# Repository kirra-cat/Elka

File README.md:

# Elka
Электронно-новогоднее, с Cortex и C... Вообщем, это инженерная ёлочка:)

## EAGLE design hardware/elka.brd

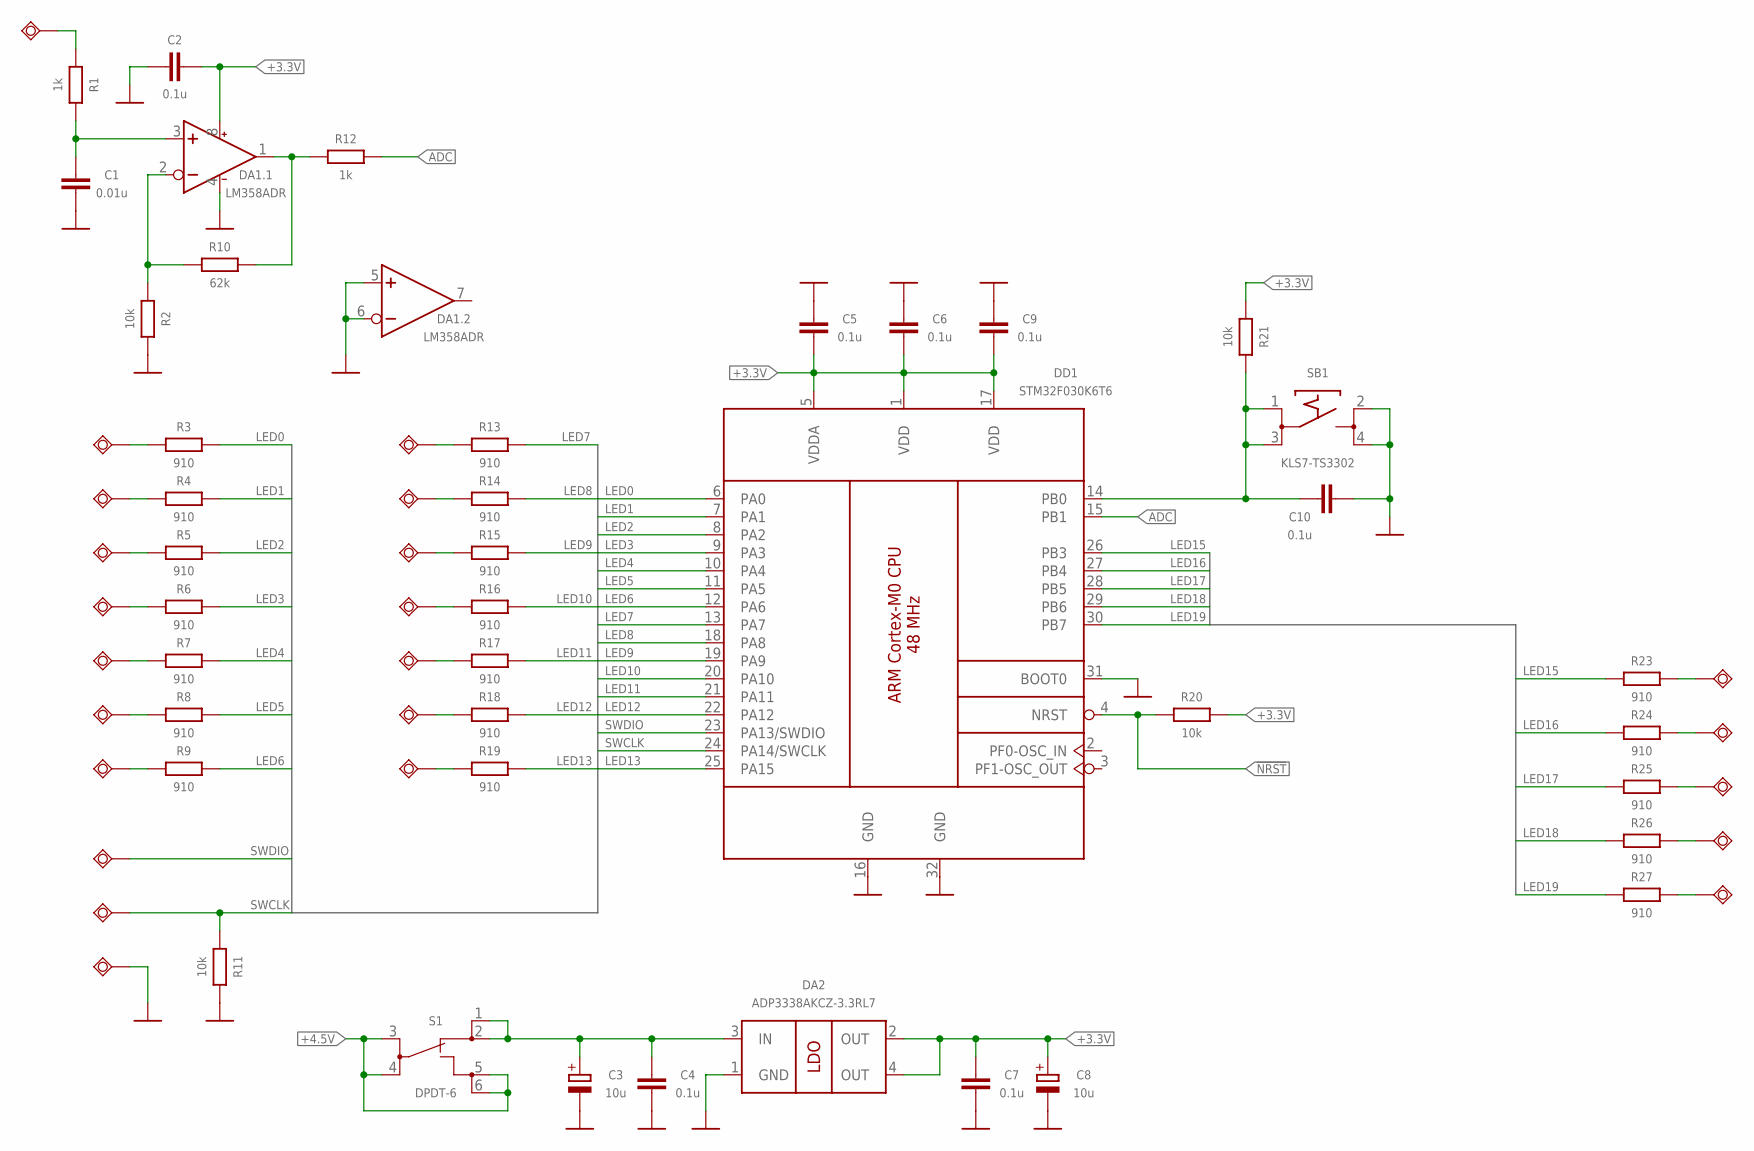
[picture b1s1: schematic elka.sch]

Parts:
C1: 0.01u; SMD0603
C2, C4, C5, C6, C7, C9, C10: 0.1u; SMD0603
C3, C8: 10u; SMC_B
DA1: LM358ADR; SOIC8
DA2: ADP3338AKCZ-3.3RL7; SOT223-W
DD1: STM32F030K6T6; LQFP32
R1, R12: 1k; SMD0603
R2, R11, R20, R21: 10k; SMD0603
R3, R4, R5, R6, R7, R8, R9, R13, R14, R15, R16, R17, R18, R19, R23, R24, R25, R26, R27: 910; SMD0603
R10: 62k; SMD0603
S1: DPDT-6; DPDT
SB1: KLS7-TS3302
TP1, TP2, TP3, TP4, TP5, TP6, TP7, TP8, TP9, TP10, TP11, TP12, TP13, TP14, TP15, TP16, TP17, TP19, TP20, TP21, TP22, TP23, TP24: TPSQTP20R; TP20R

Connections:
!NRST: DD1.4 (NRST), R20.1
+3.3V: C2.2, C5.2, C6.2, C7.1, C8.+, C9.2, DA1.8 (VCC+), DA2.2 (OUT), DA2.4 (OUT), DD1.1 (VDD), DD1.5 (VDDA), DD1.17 (VDD), R20.2, R21.2
+4.5V: S1.3, S1.4, S1.5, S1.6
ADC: DD1.15 (PB1), R12.1
GND: C1.2, C2.1, C3.-, C4.2, C5.1, C6.1, C7.2, C8.-, C9.1, C10.2, DA1.4 (VCC-), DA1.5 (IN+), DA1.6 (IN-), DA2.1 (GND), DD1.16 (GND), DD1.31 (BOOT0), DD1.32 (GND), R2.1, R11.2, SB1.2, SB1.4, TP1.TP
LED0: DD1.6 (PA0), R3.1
LED1: DD1.7 (PA1), R4.1
LED2: DD1.8 (PA2), R5.1
LED3: DD1.9 (PA3), R6.1
LED4: DD1.10 (PA4), R7.1
LED5: DD1.11 (PA5), R8.1
LED6: DD1.12 (PA6), R9.1
LED7: DD1.13 (PA7), R13.1
LED8: DD1.18 (PA8), R14.1
LED9: DD1.19 (PA9), R15.1
LED10: DD1.20 (PA10), R16.1
LED11: DD1.21 (PA11), R17.1
LED12: DD1.22 (PA12), R18.1
LED13: DD1.25 (PA15), R19.1
LED15: DD1.26 (PB3), R23.1
LED16: DD1.27 (PB4), R24.1
LED17: DD1.28 (PB5), R25.1
LED18: DD1.29 (PB6), R26.1
LED19: DD1.30 (PB7), R27.1
unnamed: R14.2, TP2.TP
unnamed: C1.1, DA1.3 (IN+), R1.1
unnamed: R15.2, TP3.TP
unnamed: R16.2, TP4.TP
unnamed: R17.2, TP5.TP
unnamed: R18.2, TP6.TP
unnamed: DA1.2 (IN-), R2.2, R10.2
unnamed: R19.2, TP9.TP
unnamed: DA1.1 (OUT), R10.1, R12.2
unnamed: R3.2, TP10.TP
unnamed: R4.2, TP11.TP
unnamed: R5.2, TP12.TP
unnamed: R6.2, TP13.TP
unnamed: R7.2, TP14.TP
unnamed: R8.2, TP15.TP
unnamed: R13.2, TP17.TP
unnamed: R9.2, TP16.TP
unnamed: C3.+, C4.1, DA2.3 (IN), S1.1, S1.2
unnamed: R23.2, TP19.TP
unnamed: R24.2, TP20.TP
unnamed: R25.2, TP21.TP
unnamed: R26.2, TP22.TP
unnamed: R27.2, TP23.TP
unnamed: C10.1, DD1.14 (PB0), R21.1, SB1.1, SB1.3
unnamed: R1.2, TP24.TP
SWCLK: DD1.24 (PA14/SWCLK), R11.1, TP8.TP
SWDIO: DD1.23 (PA13/SWDIO), TP7.TP

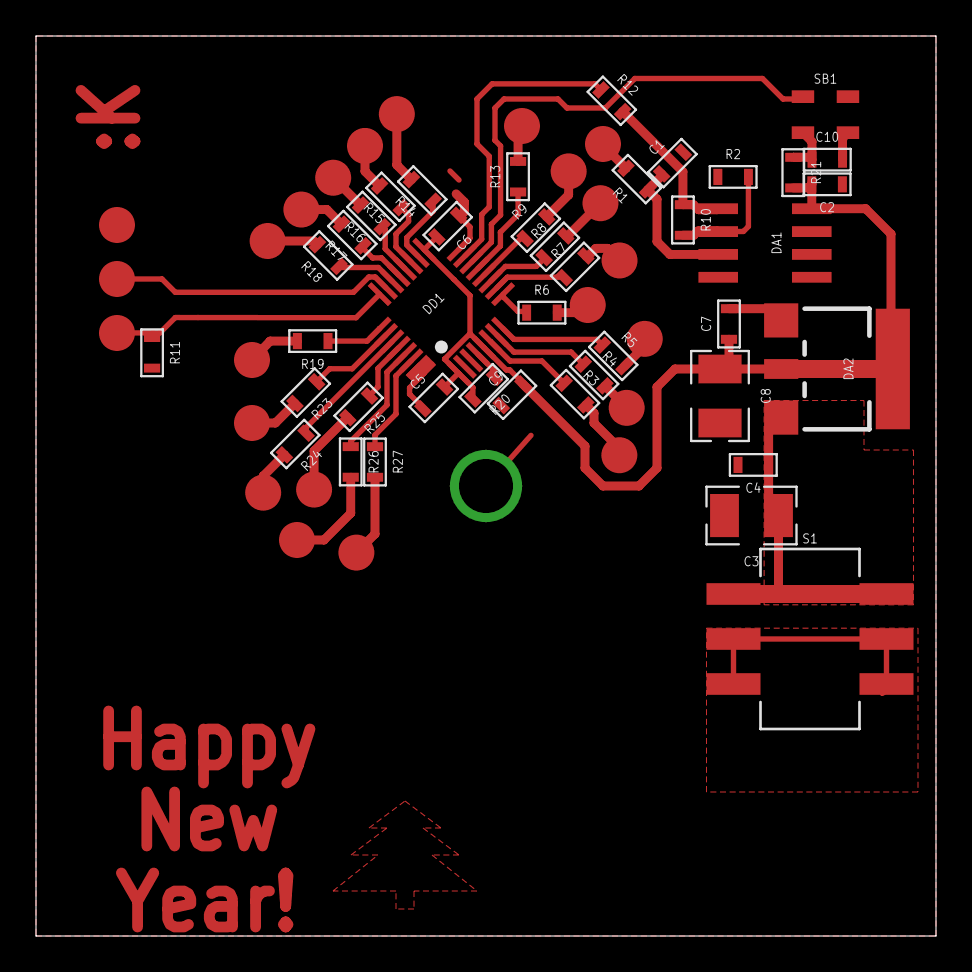
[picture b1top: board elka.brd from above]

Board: 2 copper layers, 50.0 x 50.0 mm, 64 parts (0 on the bottom side), 51 nets.

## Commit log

2016-12-11 Предварительный вариант трассировки платы
2016-12-18 Окончательный (надеюсь) вариант трассировки
